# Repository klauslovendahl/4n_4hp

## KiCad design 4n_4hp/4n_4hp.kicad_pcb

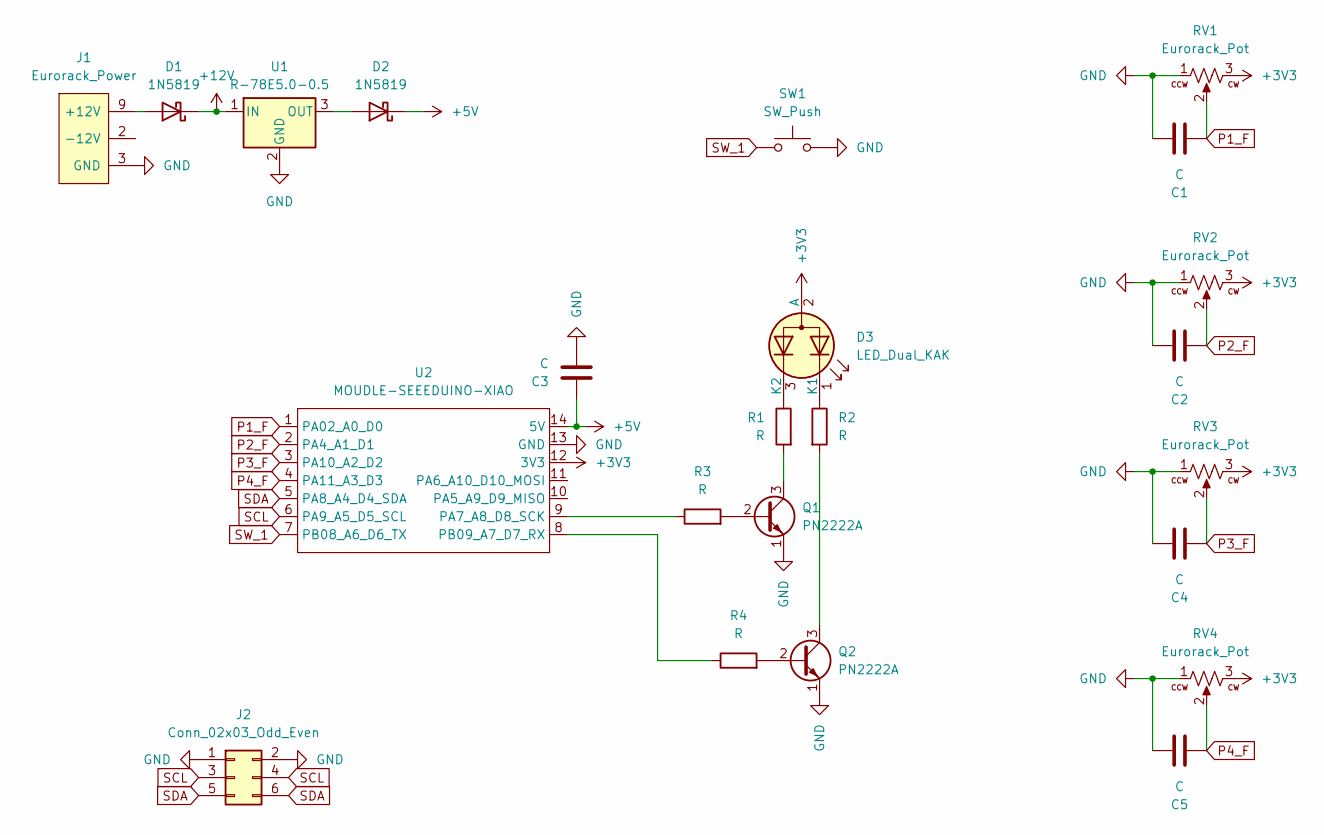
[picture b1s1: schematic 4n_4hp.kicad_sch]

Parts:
C1, C2, C3, C4, C5: C; C_Disc_D5.0mm_W2.5mm_P2.50mm
D1, D2: 1N5819; D_DO-41_SOD81_P10.16mm_Horizontal
D3: LED_Dual_KAK; LED_D3.0mm-3
J1: Eurorack_Power; Eurorack_Power_2x5_Shrouded_Lock; MPN 302-S101
J2: Conn_02x03_Odd_Even; PinHeader_2x03_P2.54mm_Vertical
Q1, Q2: PN2222A; TO-92_Inline
R1, R2, R3, R4: R; R_Axial_DIN0204_L3.6mm_D1.6mm_P2.54mm_Vertical
RV1, RV2, RV3, RV4: Eurorack_Pot; Potentiometer_Alpha_R0904N; MPN R0904N-???? L-25KQ/LWS
SW1: SW_Push; Tactile_Switch_6mm
U1: R-78E5.0-0.5; Converter_DCDC_RECOM_R-78E-0.5_THT
U2: MOUDLE-SEEEDUINO-XIAO; MOUDLE14P-2.54-21X17.8MM

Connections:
+3V3: D3.2 (A), RV1.3, RV2.3, RV3.3, RV4.3, U2.12 (3V3)
+5V: C3.1, D2.1 (K), U2.14 (5V)
+12V: D1.1 (K), U1.1 (IN)
GND: C1.2, C2.2, C3.2, C4.2, C5.2, J1.3 (GND), J1.4 (GND), J1.5 (GND), J1.6 (GND), J1.7 (GND), J1.8 (GND), J2.1, J2.2, Q1.1 (E), Q2.1 (E), RV1.1, RV2.1, RV3.1, RV4.1, SW1.2, U1.2 (GND), U2.13 (GND)
unnamed: D1.2 (A), J1.9 (+12V), J1.10 (+12V)
unnamed: D2.2 (A), U1.3 (OUT)
unnamed: D3.1 (K1), R2.1
unnamed: D3.3 (K2), R1.1
unnamed: J1.1 (-12V), J1.2 (-12V)
unnamed: Q1.2 (B), R3.2
unnamed: Q1.3 (C), R1.2
unnamed: Q2.2 (B), R4.2
unnamed: Q2.3 (C), R2.2
unnamed: R3.1, U2.9 (PA7_A8_D8_SCK)
unnamed: R4.1, U2.8 (PB09_A7_D7_RX)
P1_F: C1.1, RV1.2, U2.1 (PA02_A0_D0)
P2_F: C2.1, RV2.2, U2.2 (PA4_A1_D1)
P3_F: C4.1, RV3.2, U2.3 (PA10_A2_D2)
P4_F: C5.1, RV4.2, U2.4 (PA11_A3_D3)
SCL: J2.3, J2.4, U2.6 (PA9_A5_D5_SCL)
SDA: J2.5, J2.6, U2.5 (PA8_A4_D4_SDA)
SW_1: SW1.1, U2.7 (PB08_A6_D6_TX)

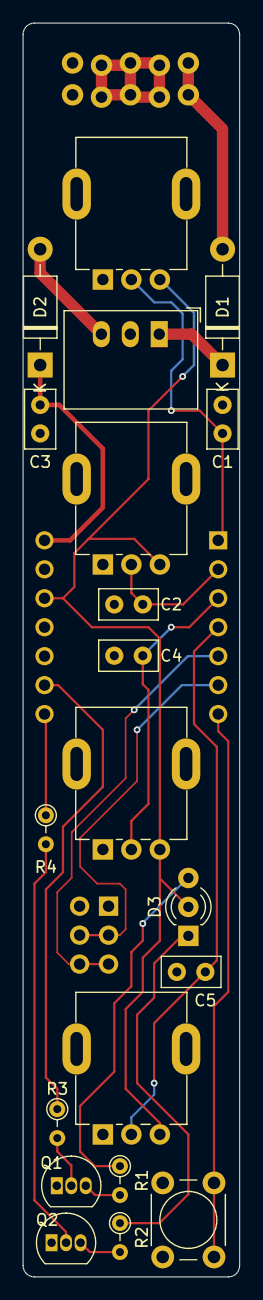
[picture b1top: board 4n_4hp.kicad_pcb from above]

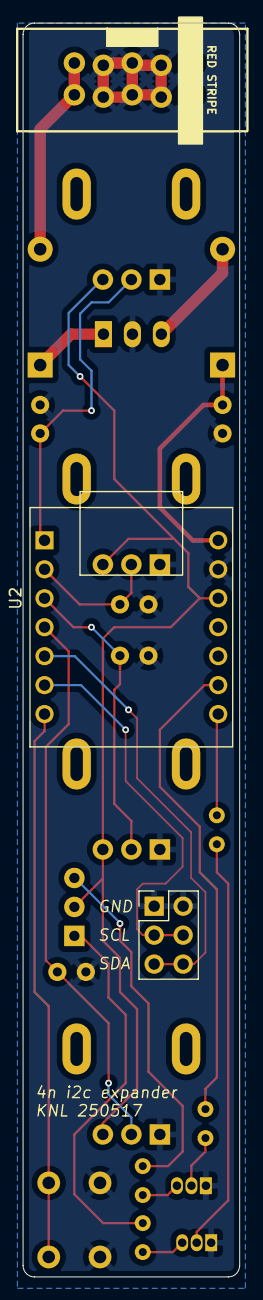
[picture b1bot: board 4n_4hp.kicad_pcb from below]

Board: 2 copper layers, 19.0 x 110.0 mm, 23 parts (3 on the bottom side), 22 nets.

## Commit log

2025-05-17 Add files via upload
    initial version ordered from OSHPark 250517
